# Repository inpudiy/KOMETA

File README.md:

# KOMETA

KOMETA is a split keyboard built around Choc switches, designed for wireless operation with Pro Micro–sized microcontrollers. Its key feature is a mid-mount, hot-swappablecontroller design. To enable this, the PCB includes a USB-C port cutout, ensuring compatibility with popular wireless boards like: nice!nano or SuperMini

[Build Guide](BUILD.md) - [ZMK Firmware](https://github.com/inpudiy/zmk-KOMETA)

## Features

- Pro Micro-format microcontroller, compatible with mid-mount hot-swap installation
- Optimized for wireless: hardware power switch, reset button, battery solder pads, no LEDs, and ZMK firmware
- Choc V1/V2 switches with MX spacing (19 × 19 mm)
- 42-key layout with column stagger, inspired by the Jian keyboard
- 3D-printed case

## PCB Image

## Case

The repository includes two case variants: the original with angular walls, and a rounded community fork by @max_shu.

## BOM (Bill of Materials)

| Component                                                    | Qty |
| ------------------------------------------------------------ | --- |
| Pro Micro board: Super Mini nRF52840 / nice!nano             | 2   |
| MSK12C02 Slide Switch                                        | 2   |
| 301230 battery                                               | 2   |
| TS342A2P                                                     | 2   |
| Silicone bumpers (6x2 mm)                                    | 8   |
| Machine Pin Header Female                                    | 48  |
| 50mm Industrial H62 brass wire 0.5mm thickness               | 1   |
| PG1350 hot-swap socket                                       | 42  |
| Diode 1N4148WS (SOD-323)                                     | 42  |
| CHOC V1/2 switches                                           | 42  |
| M2 Hexagon Nut                                               | 12  |
| M2 Thin Flat Head Screw 9mm                                  | 12  |

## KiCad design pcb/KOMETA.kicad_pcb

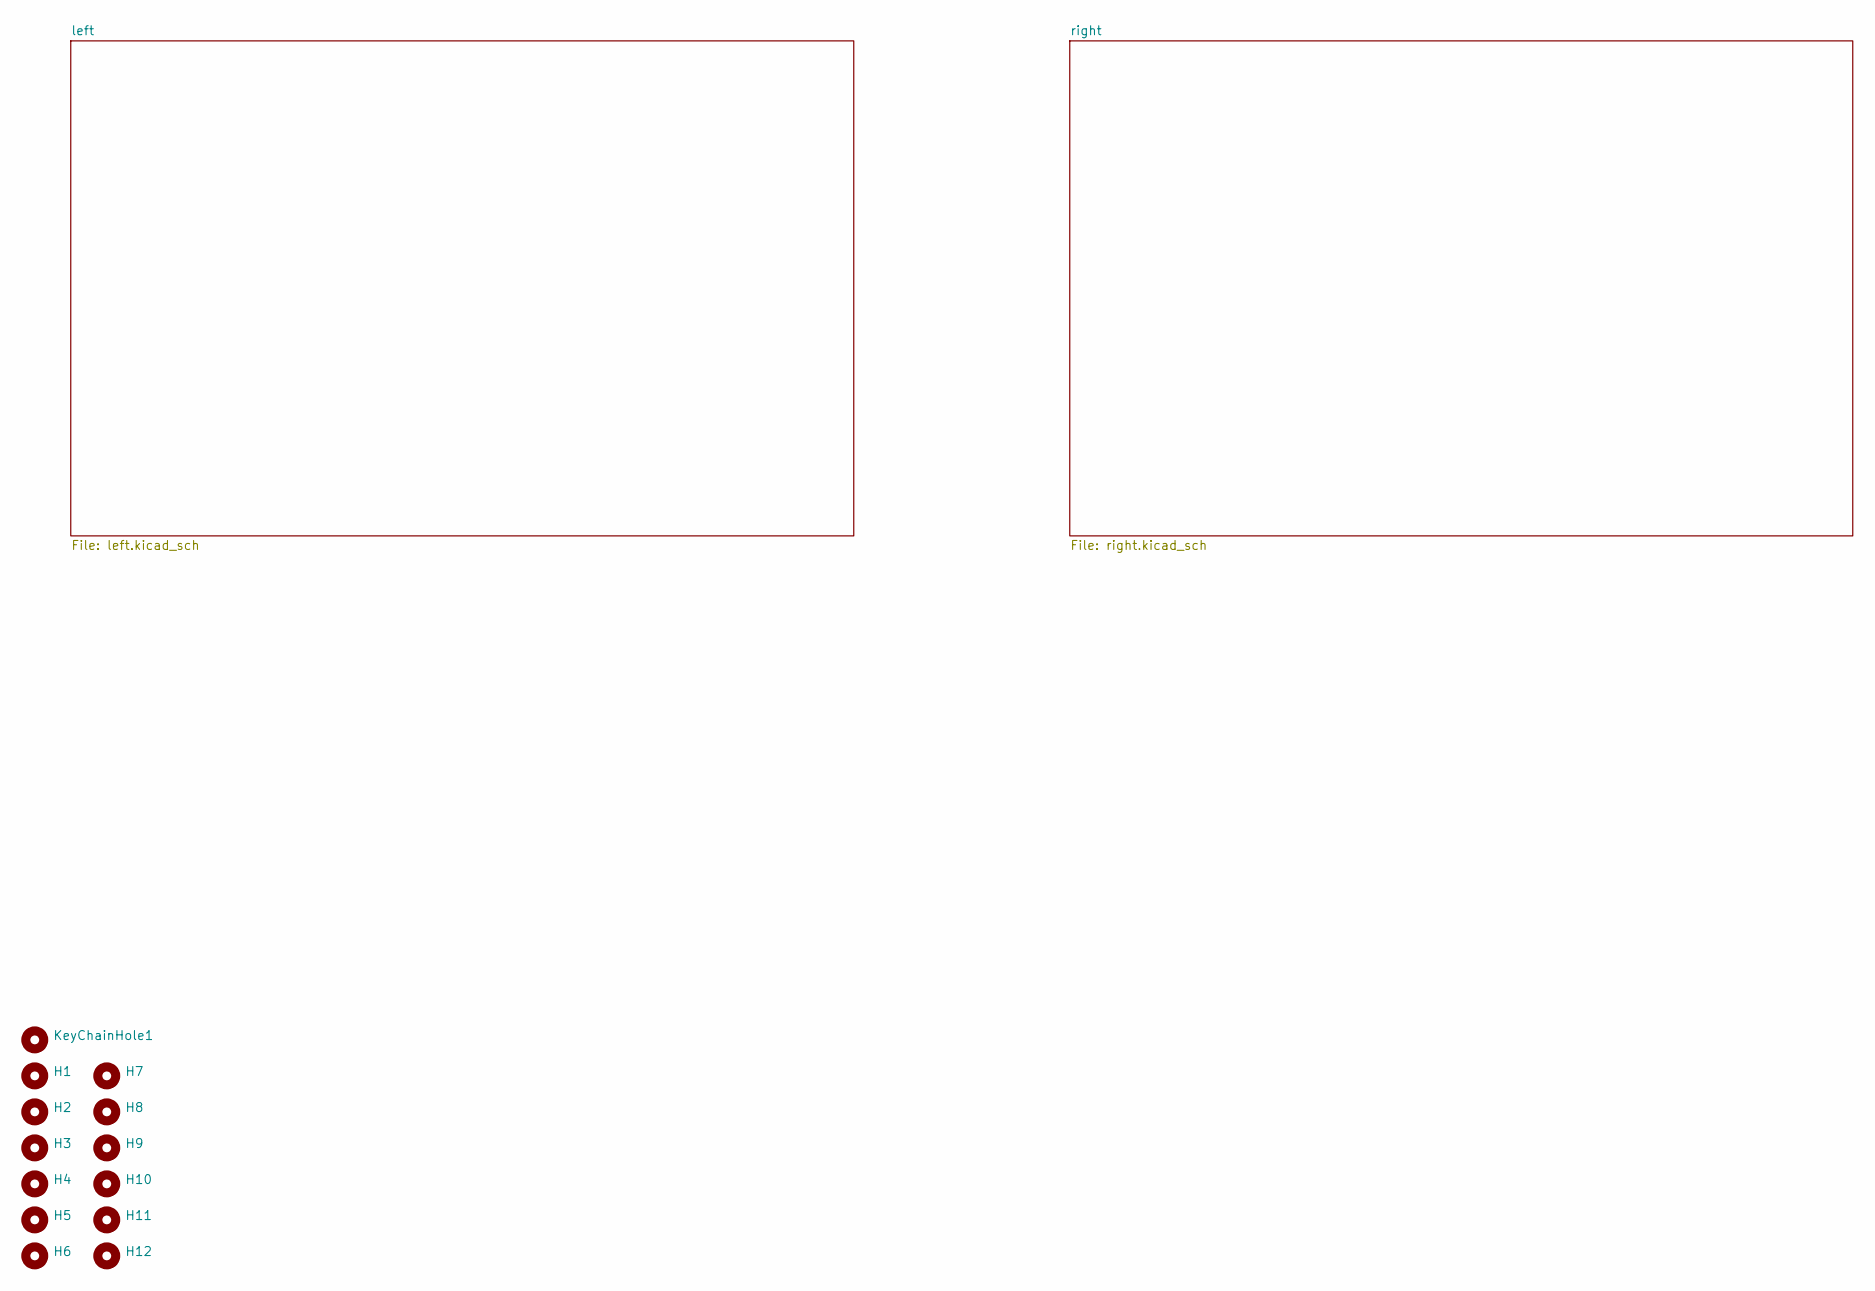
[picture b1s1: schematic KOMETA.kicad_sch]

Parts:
H1, H2, H3, H4, H5, H6, H7, H8, H9, H10, H11, H12: M2 Hole
KeyChainHole1: M5 hole

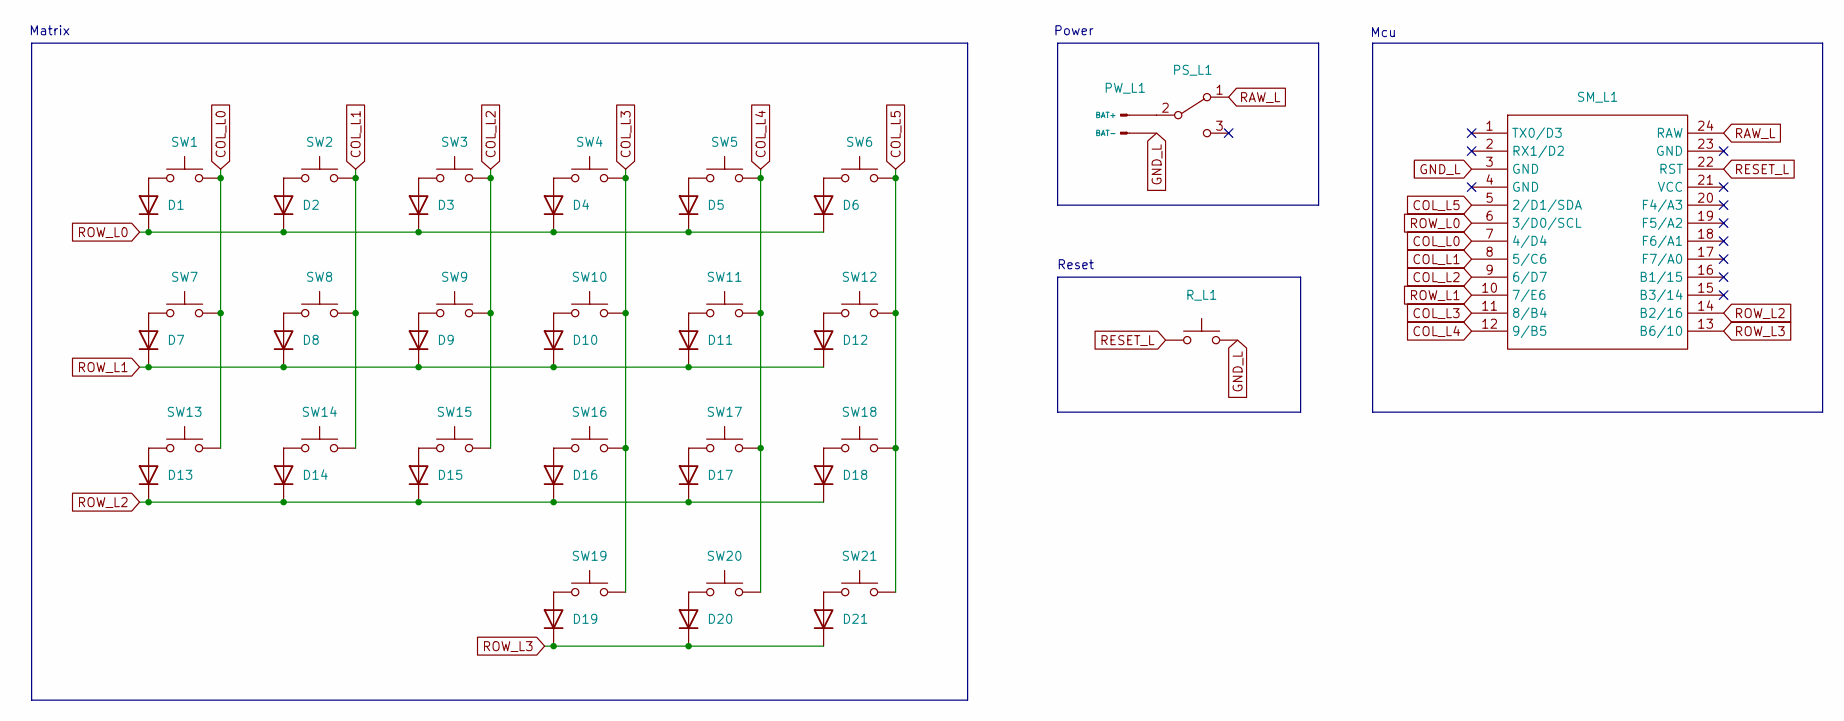
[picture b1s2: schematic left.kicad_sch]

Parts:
D1, D2, D3, D4, D5, D6, D7, D8, D9, D10, D11, D12, D13, D14, D15, D16, D17, D18, D19, D20, D21: Diode
PS_L1: MSK-12C02
PW_L1: Battery
R_L1: Reset
SM_L1: SuperMini
SW1, SW2, SW3, SW4, SW5, SW6, SW7, SW8, SW9, SW10, SW11, SW12, SW13, SW14, SW15, SW16, SW17, SW18, SW19, SW20, SW21: ChocV2

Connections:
COL_L0: SM_L1.7 (4/D4), SW1.2, SW7.2, SW13.2
COL_L1: SM_L1.8 (5/C6), SW2.2, SW8.2, SW14.2
COL_L2: SM_L1.9 (6/D7), SW3.2, SW9.2, SW15.2
COL_L3: SM_L1.11 (8/B4), SW4.2, SW10.2, SW16.2, SW19.2
COL_L4: SM_L1.12 (9/B5), SW5.2, SW11.2, SW17.2, SW20.2
COL_L5: SM_L1.5 (2/D1/SDA), SW6.2, SW12.2, SW18.2, SW21.2
GND_L: PW_L1.2 (BAT-), R_L1.2, SM_L1.3 (GND)
unnamed: D1.2 (A), SW1.1
unnamed: D2.2 (A), SW2.1
unnamed: D3.2 (A), SW3.1
unnamed: D4.2 (A), SW4.1
unnamed: D5.2 (A), SW5.1
unnamed: D6.2 (A), SW6.1
unnamed: D7.2 (A), SW7.1
unnamed: D8.2 (A), SW8.1
unnamed: D9.2 (A), SW9.1
unnamed: D10.2 (A), SW10.1
unnamed: D11.2 (A), SW11.1
unnamed: D12.2 (A), SW12.1
unnamed: D13.2 (A), SW13.1
unnamed: D14.2 (A), SW14.1
unnamed: D15.2 (A), SW15.1
unnamed: D16.2 (A), SW16.1
unnamed: D17.2 (A), SW17.1
unnamed: D18.2 (A), SW18.1
unnamed: D19.2 (A), SW19.1
unnamed: D20.2 (A), SW20.1
unnamed: D21.2 (A), SW21.1
unnamed: PS_L1.2 (B), PW_L1.1 (BAT+)
RAW_L: PS_L1.1 (A), SM_L1.24 (RAW)
RESET_L: R_L1.1, SM_L1.22 (RST)
ROW_L0: D1.1 (K), D2.1 (K), D3.1 (K), D4.1 (K), D5.1 (K), D6.1 (K), SM_L1.6 (3/D0/SCL)
ROW_L1: D7.1 (K), D8.1 (K), D9.1 (K), D10.1 (K), D11.1 (K), D12.1 (K), SM_L1.10 (7/E6)
ROW_L2: D13.1 (K), D14.1 (K), D15.1 (K), D16.1 (K), D17.1 (K), D18.1 (K), SM_L1.14 (B2/16)
ROW_L3: D19.1 (K), D20.1 (K), D21.1 (K), SM_L1.13 (B6/10)

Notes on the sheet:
Reset
Power
Matrix
Mcu

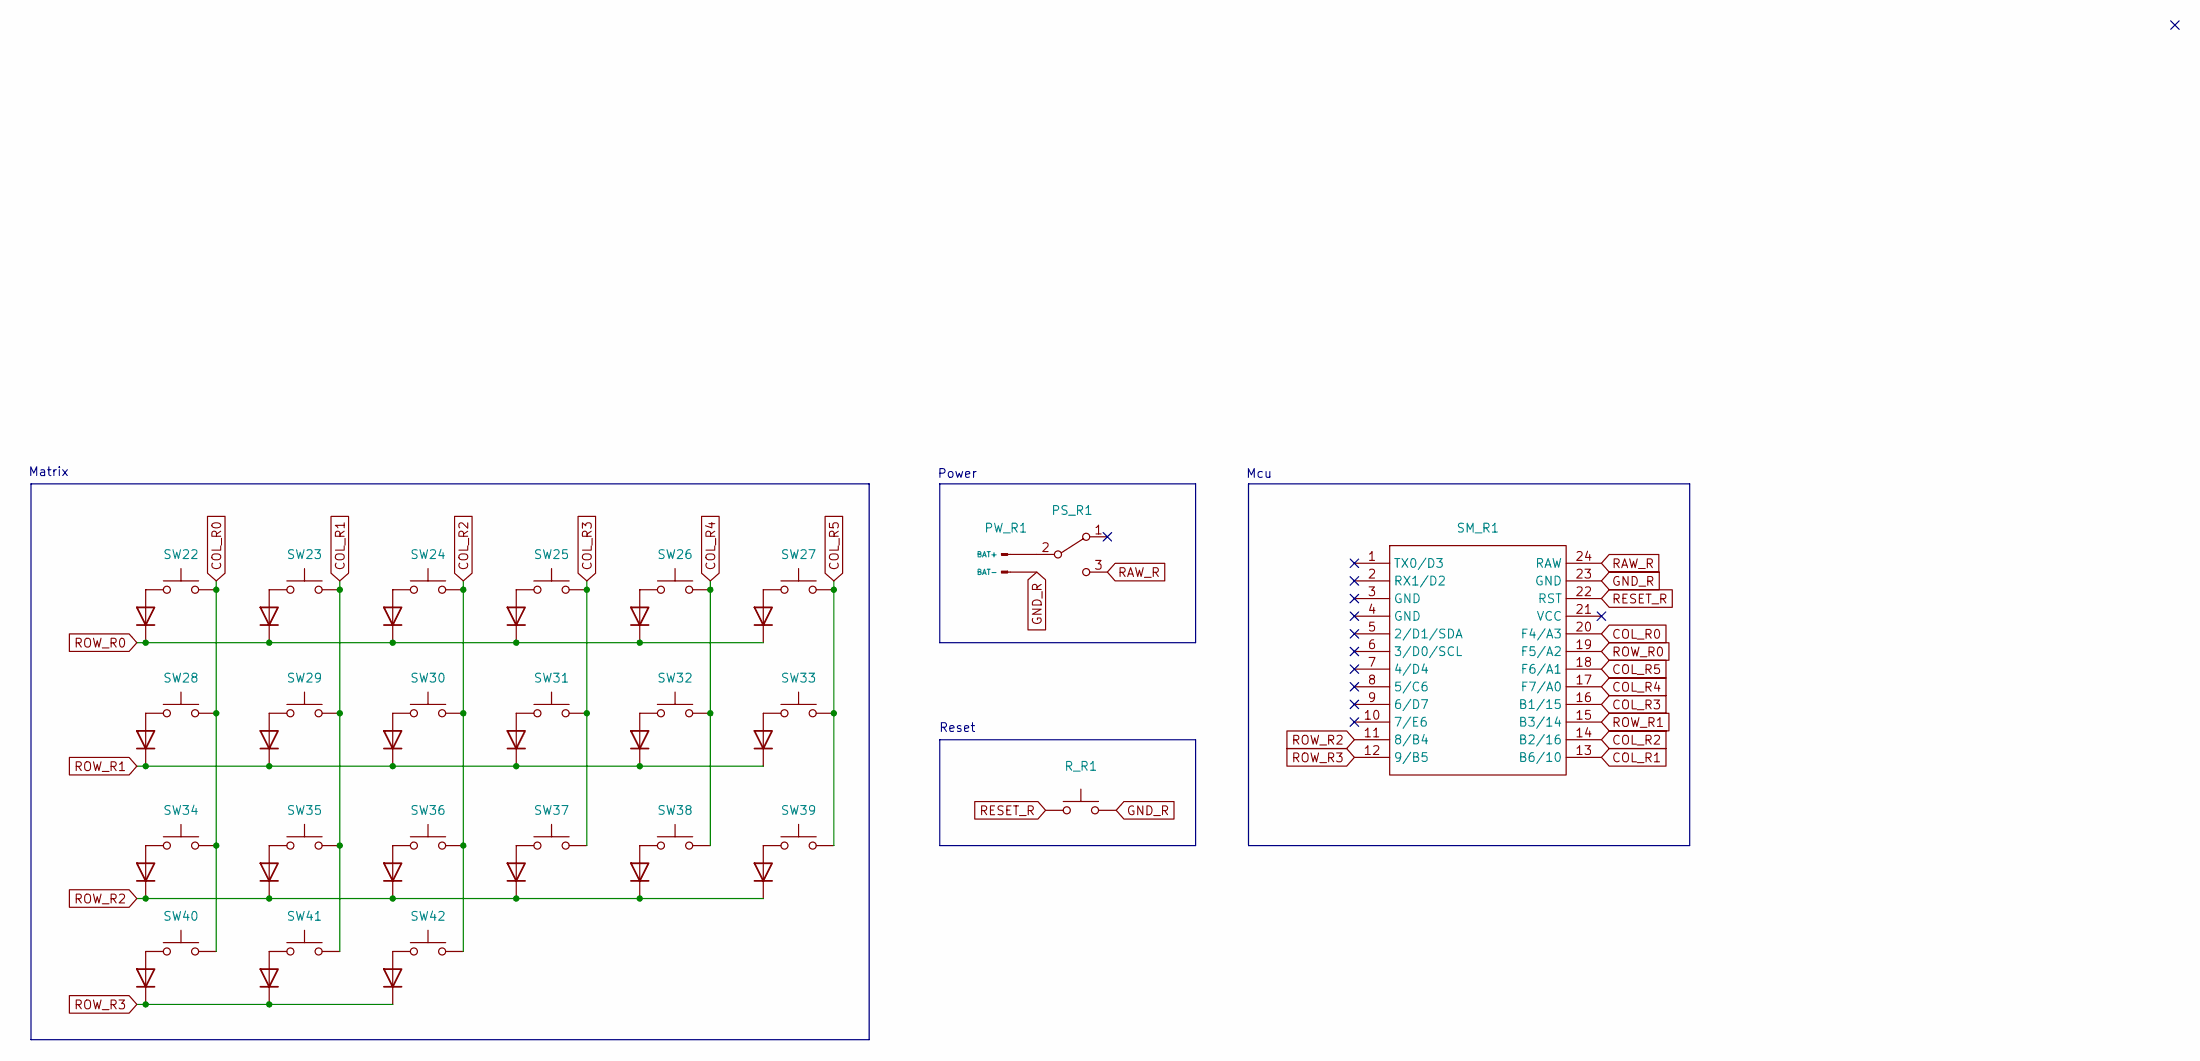
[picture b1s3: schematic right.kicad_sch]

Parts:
D22, D23, D24, D25, D26, D27, D28, D29, D30, D31, D32, D33, D34, D35, D36, D37, D38, D39, D40, D41, D42: Diode
PS_R1: MSK-12C02
PW_R1: Battery
R_R1: Reset
SM_R1: SuperMini
SW22, SW23, SW24, SW25, SW26, SW27, SW28, SW29, SW30, SW31, SW32, SW33, SW34, SW35, SW36, SW37, SW38, SW39, SW40, SW41, SW42: ChocV2

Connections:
COL_R0: SM_R1.20 (F4/A3), SW22.2, SW28.2, SW34.2, SW40.2
COL_R1: SM_R1.13 (B6/10), SW23.2, SW29.2, SW35.2, SW41.2
COL_R2: SM_R1.14 (B2/16), SW24.2, SW30.2, SW36.2, SW42.2
COL_R3: SM_R1.16 (B1/15), SW25.2, SW31.2, SW37.2
COL_R4: SM_R1.17 (F7/A0), SW26.2, SW32.2, SW38.2
COL_R5: SM_R1.18 (F6/A1), SW27.2, SW33.2, SW39.2
GND_R: PW_R1.2 (BAT-), R_R1.2, SM_R1.23 (GND)
unnamed: D22.2 (A), SW22.1
unnamed: D23.2 (A), SW23.1
unnamed: D24.2 (A), SW24.1
unnamed: D25.2 (A), SW25.1
unnamed: D26.2 (A), SW26.1
unnamed: D27.2 (A), SW27.1
unnamed: D28.2 (A), SW28.1
unnamed: D29.2 (A), SW29.1
unnamed: D30.2 (A), SW30.1
unnamed: D31.2 (A), SW31.1
unnamed: D32.2 (A), SW32.1
unnamed: D33.2 (A), SW33.1
unnamed: D34.2 (A), SW34.1
unnamed: D35.2 (A), SW35.1
unnamed: D36.2 (A), SW36.1
unnamed: D37.2 (A), SW37.1
unnamed: D38.2 (A), SW38.1
unnamed: D39.2 (A), SW39.1
unnamed: D40.2 (A), SW40.1
unnamed: D41.2 (A), SW41.1
unnamed: D42.2 (A), SW42.1
unnamed: PS_R1.2 (B), PW_R1.1 (BAT+)
RAW_R: PS_R1.3 (C), SM_R1.24 (RAW)
RESET_R: R_R1.1, SM_R1.22 (RST)
ROW_R0: D22.1 (K), D23.1 (K), D24.1 (K), D25.1 (K), D26.1 (K), D27.1 (K), SM_R1.19 (F5/A2)
ROW_R1: D28.1 (K), D29.1 (K), D30.1 (K), D31.1 (K), D32.1 (K), D33.1 (K), SM_R1.15 (B3/14)
ROW_R2: D34.1 (K), D35.1 (K), D36.1 (K), D37.1 (K), D38.1 (K), D39.1 (K), SM_R1.11 (8/B4)
ROW_R3: D40.1 (K), D41.1 (K), D42.1 (K), SM_R1.12 (9/B5)

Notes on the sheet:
Reset
Power
Mcu
Matrix

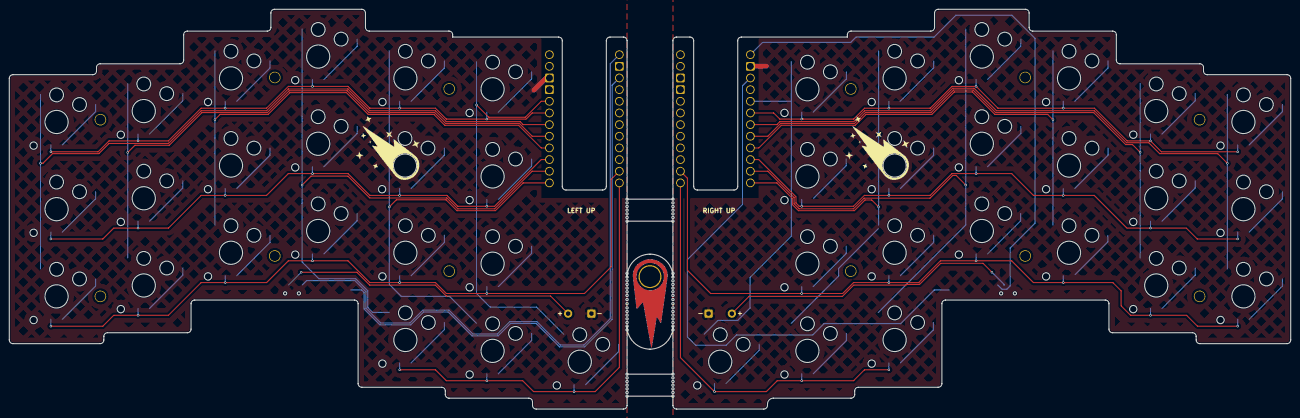
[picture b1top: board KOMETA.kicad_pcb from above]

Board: 2 copper layers, 279.2 x 87.1 mm, 113 parts (0 on the bottom side), 70 nets.

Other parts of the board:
BH: Val**; BreakHole
BH#2, BH#3, BH#4, BH#5, BH#6, BH#7, BH#8: Val**; BreakHole

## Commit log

2025-05-22 upload source
2025-06-04 update silkscreen
2025-06-04 add pcb image
2025-06-05 update footrpint
2025-06-05 update footprint
2025-06-05 fix silkscreen
2025-06-05 update images
2025-06-05 fix images
2025-06-05 fix link
2025-06-14 Fix aka name
2025-06-18 fix EdgeCuts
2025-06-18 update links
2025-07-08 Rename image/all.png to image/gallery/all.png
2025-07-08 add case files & update readme
2025-07-19 add support choc v1
2025-07-19 update BOM
2025-09-12 upload v1.1
2025-09-16 update pcb
2025-10-01 upload buid picture
2025-10-01 write solder guide
2025-10-02 add flash guide
2025-10-02 start doc about mid_mount
2025-10-02 clear
2025-10-09 Create LICENSE
2025-10-09 Update LICENSE
2025-10-25 some fix
2025-12-03 rename directory
2025-12-03 update footpint
2025-12-06 fix: misnamed left/right no pattern plates
2026-01-11 add led sh and pretty
2026-01-20 Added rgb led, made reset and powerswitch twoside solderable
2026-01-20 Little fix
2026-01-20 Some fixes
2026-02-05 Experimental KS27/KS33 support
2026-03-20 Remove ks27/ks33 support, fix mcu board cutout
2026-04-06 upload case fork
